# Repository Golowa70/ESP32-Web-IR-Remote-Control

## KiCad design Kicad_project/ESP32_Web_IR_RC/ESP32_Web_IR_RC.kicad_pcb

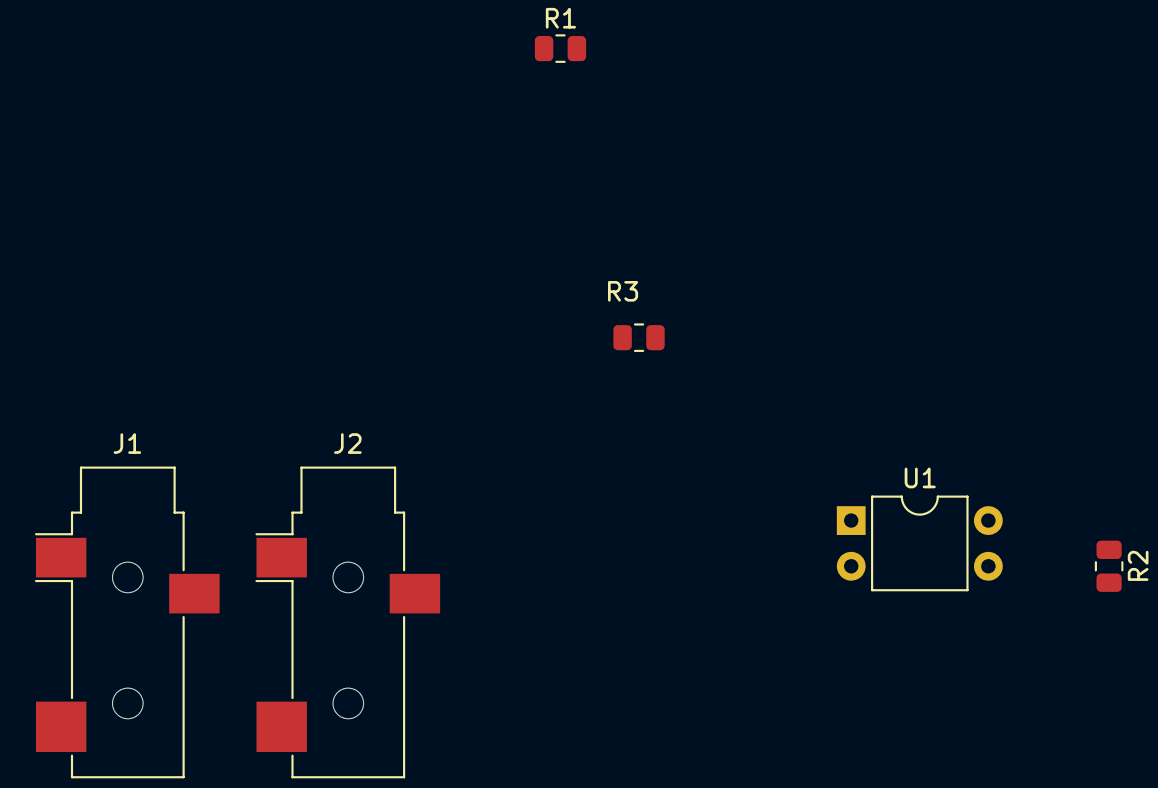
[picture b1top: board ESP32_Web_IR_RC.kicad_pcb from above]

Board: 2 copper layers, 6 parts (0 on the bottom side), 5 nets, no tracks yet.

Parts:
J1: Trigger_input; Jack_3.5mm_CUI_SJ-3523-SMT_Horizontal
J2: IR_output; Jack_3.5mm_CUI_SJ-3523-SMT_Horizontal
R1, R2: 2k; R_0805_2012Metric
R3: 10k; R_0805_2012Metric
U1: PC817; DIP-4_W7.62mm

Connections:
unnamed: J1.S, U1.2
unnamed: J1.T, R1.1
unnamed: R1.2, U1.1
unnamed: R2.1, U1.4
unnamed: R3.2, U1.3

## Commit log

2024-01-01 Starting
2024-01-03 Changed "deviceCommmandHandler" function
